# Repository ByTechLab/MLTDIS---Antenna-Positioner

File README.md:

<div align="center">
    
</div>

Antenna Positioner

### Read more at BYTECHLAB:

<table style="width: 100%; border: none;" cellspacing="0" cellpadding="0" border="0">
  <tr>
    <td></td>
    <td>https://bytechlab.com/2026/11/antenna-positioner/</td>
  </tr>
</table>

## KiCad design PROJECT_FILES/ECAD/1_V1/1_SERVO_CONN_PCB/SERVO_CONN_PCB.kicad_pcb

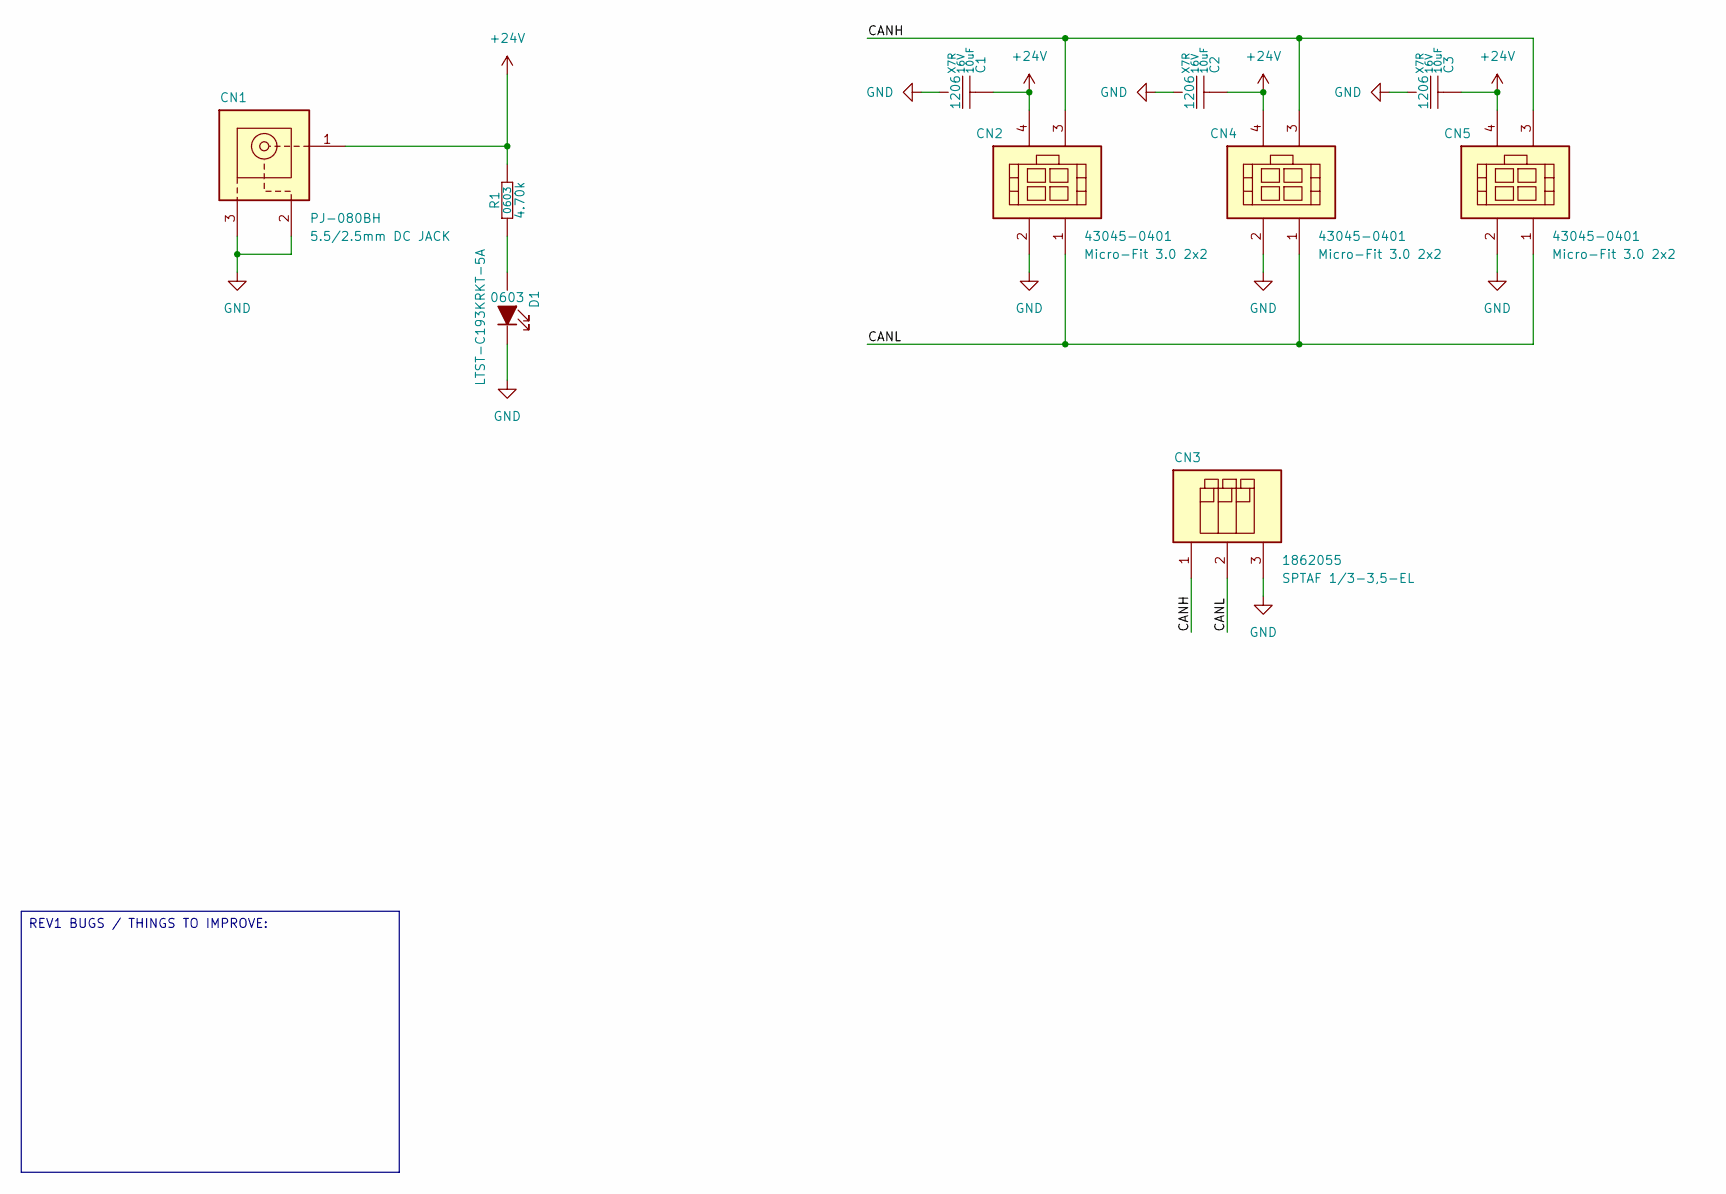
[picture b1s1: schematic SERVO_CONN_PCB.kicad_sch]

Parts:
C1, C2, C3: 10uF; C_SMD_1206; Tolerance ±10%; MPN GRM31CR71C106KAC7
CN1: CN_PJ-080BH; Voltage_Max 36V; MPN PJ-080BH
CN2, CN4, CN5: CN_43045-0401; Voltage_Max 600V; MPN 43045-0401
CN3: CN_1862055; Voltage_Max 160V; MPN 1862055
D1: LED_SMD_0603; MPN LTST-C193KRKT-5A
R1: 4.70k; R_SMD_0603; Tolerance 1%; MPN CRCW06034K70FKEA

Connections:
+24V: C1.1, C2.1, C3.1, CN1.1, CN2.4, CN4.4, CN5.4, R1.2
/CANH: CN2.3, CN3.1, CN4.3, CN5.3
/CANL: CN2.1, CN3.2, CN4.1, CN5.1
GND: C1.2, C2.2, C3.2, CN1.2, CN1.3, CN2.2, CN3.3, CN4.2, CN5.2, D1.1 (K)
unnamed: D1.2 (A), R1.1

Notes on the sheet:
REV1 BUGS / THINGS TO IMPROVE:

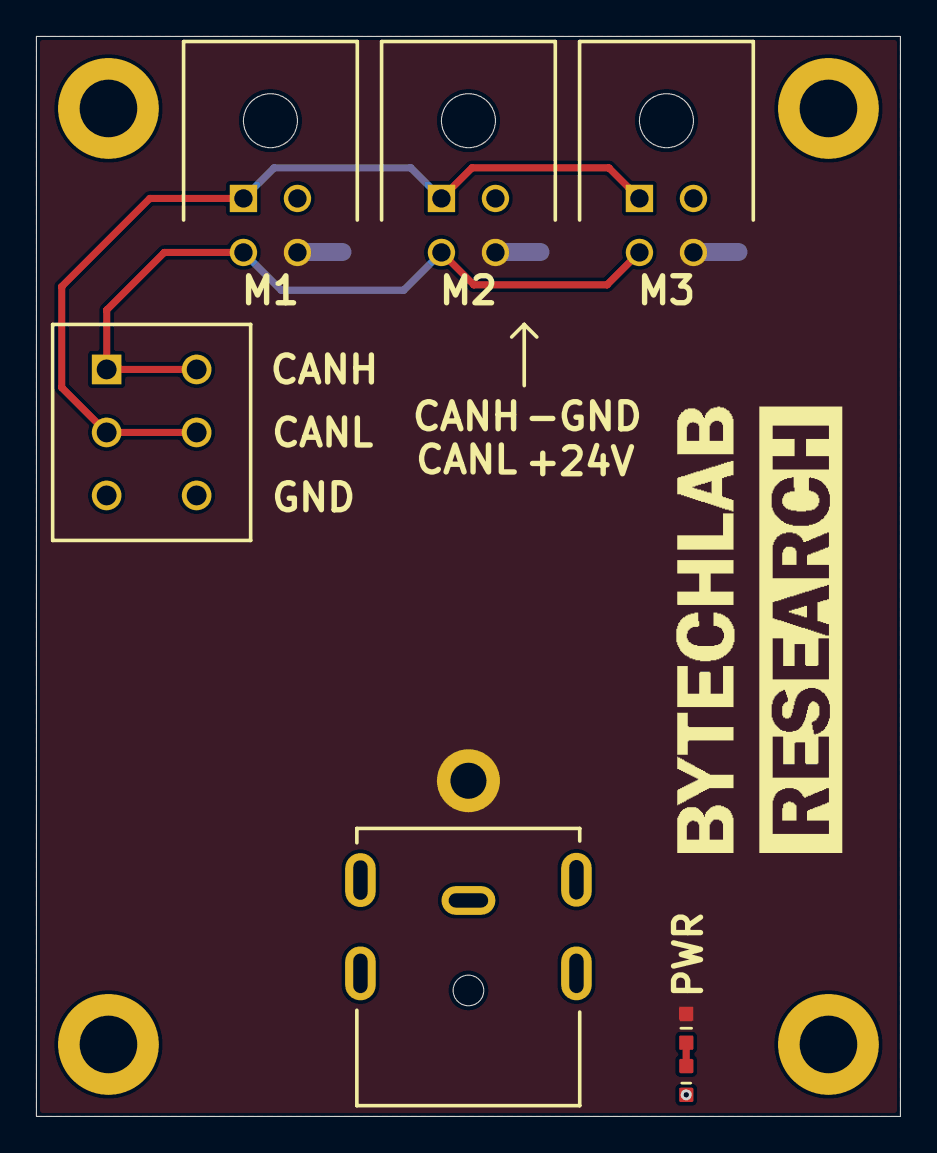
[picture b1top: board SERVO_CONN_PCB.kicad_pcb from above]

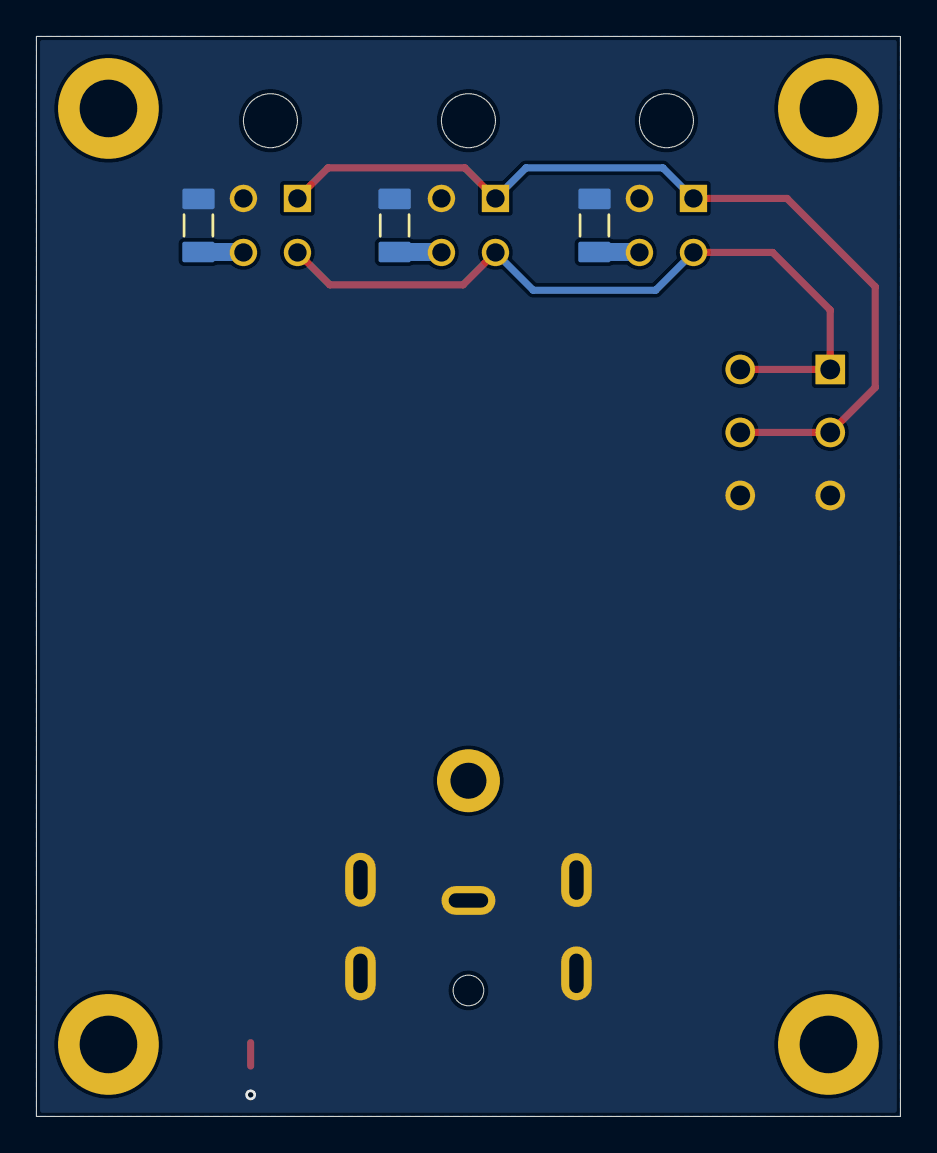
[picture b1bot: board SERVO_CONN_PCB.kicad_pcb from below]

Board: 2 copper layers, 48.0 x 60.0 mm, 10 parts (3 on the bottom side), 5 nets.
